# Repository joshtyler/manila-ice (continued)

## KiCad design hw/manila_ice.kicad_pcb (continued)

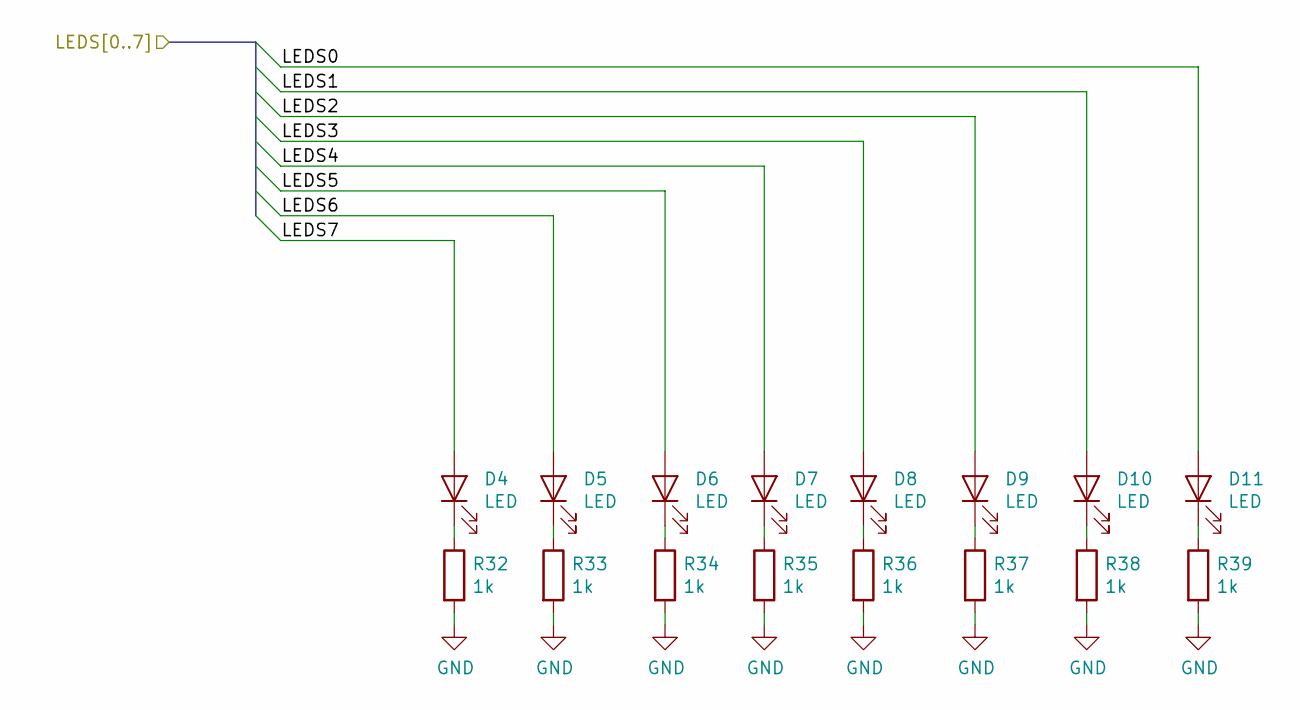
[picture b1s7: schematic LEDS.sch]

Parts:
D4, D5, D6, D7, D8, D9, D10, D11: LED; D_0805_2012Metric_Castellated; LCSC Part C84256
R32, R33, R34, R35, R36, R37, R38, R39: 1k; R_0603_1608Metric; LCSC Part C21190

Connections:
/FPGA/LED0: D11.2 (A); also elsewhere on the board
/FPGA/LED1: D10.2 (A); also elsewhere on the board
/FPGA/LED2: D9.2 (A); also elsewhere on the board
/FPGA/LED3: D8.2 (A); also elsewhere on the board
/FPGA/LED4: D7.2 (A); also elsewhere on the board
/FPGA/LED5: D6.2 (A); also elsewhere on the board
/FPGA/LED6: D5.2 (A); also elsewhere on the board
/FPGA/LED7: D4.2 (A); also elsewhere on the board
GND: R32.2, R33.2, R34.2, R35.2, R36.2, R37.2, R38.2, R39.2; also elsewhere on the board
unnamed: D4.1 (K), R32.1
unnamed: D5.1 (K), R33.1
unnamed: D6.1 (K), R34.1
unnamed: D7.1 (K), R35.1
unnamed: D8.1 (K), R36.1
unnamed: D9.1 (K), R37.1
unnamed: D10.1 (K), R38.1
unnamed: D11.1 (K), R39.1

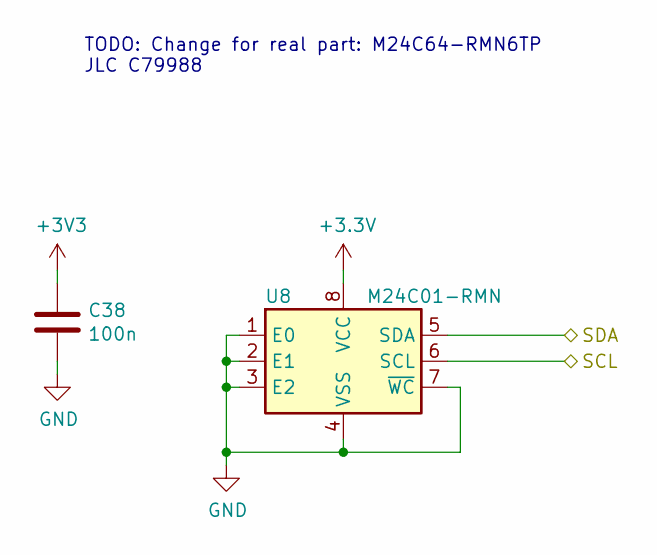
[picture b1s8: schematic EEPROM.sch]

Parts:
C38: 100n; C_0603_1608Metric; LCSC Part C14663
U8: M24C01-RMN; SOIC-8_3.9x4.9mm_P1.27mm; LCSC Part C79988

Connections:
/EEPROM/SCL: U8.6 (SCL); also elsewhere on the board
/EEPROM/SDA: U8.5 (SDA); also elsewhere on the board
GND: C38.2, U8.1 (E0), U8.2 (E1), U8.3 (E2), U8.4 (VSS), U8.7 (~WC); also elsewhere on the board

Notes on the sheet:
TODO: Change for real part: M24C64-RMN6TP JLC C79988

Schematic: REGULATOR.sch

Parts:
C10, C42, C43, C44: 22u; C_0603_1608Metric; LCSC Part C59461
C11, C41: 100n; C_0603_1608Metric; LCSC Part C14663
C12: 10p; C_0603_1608Metric; LCSC Part C1634
C39: 1n; C_0603_1608Metric; LCSC Part C1588
C40: 10n; C_0603_1608Metric; LCSC Part C57112
C45: 100u; CP_EIA-3528-21_Kemet-B; LCSC Part C16133
D12: SS54; D_SMA; LCSC Part C22452
L2: 2u2; L_Sunlord_MWSA0518; LCSC Part C408345
R43: 43k; R_0603_1608Metric; LCSC Part C23172
U3: TPS54331D; SOIC-8_3.9x4.9mm_P1.27mm; LCSC Part C9865

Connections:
+1V2: C42.1, C43.1, C44.1, C45.1, L2.2; also elsewhere on the board
/1V2_REG/BOOT: C41.1, U3.1 (BOOT)
/1V2_REG/COMP: C12.1, R43.1, U3.6 (COMP)
/1V2_REG/COMP_RC: C39.1, R43.2
/1V2_REG/FB: U3.5 (FB); also elsewhere on the board
/1V2_REG/PH: C41.2, D12.1 (K), L2.1, U3.8 (PH)
/1V2_REG/SS: C40.1, U3.4 (SS)
/5V: C10.1, C11.1, U3.2 (VIN); also elsewhere on the board
GND: C10.2, C11.2, C12.2, C39.2, C40.2, C42.2, C43.2, C44.2, C45.2, D12.2 (A), U3.7 (GND); also elsewhere on the board

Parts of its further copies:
C46, C52, C53, C54: 22u; C_0603_1608Metric; LCSC Part C59461
C47, C51: 100n; C_0603_1608Metric; LCSC Part C14663
C48: 10p; C_0603_1608Metric; LCSC Part C1634
C49: 1n; C_0603_1608Metric; LCSC Part C1588
C50: 10n; C_0603_1608Metric; LCSC Part C57112
C55: 100u; CP_EIA-3528-21_Kemet-B; LCSC Part C16133
D13: SS54; D_SMA; LCSC Part C22452
L3: 2u2; L_Sunlord_MWSA0518; LCSC Part C408345
R44: 43k; R_0603_1608Metric; LCSC Part C23172
U4: TPS54331D; SOIC-8_3.9x4.9mm_P1.27mm; LCSC Part C9865

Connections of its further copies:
/3V3_REG/BOOT: C51.1, U4.1 (BOOT)
/3V3_REG/COMP: C48.1, R44.1, U4.6 (COMP)
/3V3_REG/COMP_RC: C49.1, R44.2
/3V3_REG/FB: U4.5 (FB); also elsewhere on the board
/3V3_REG/PH: C51.2, D13.1 (K), L3.1, U4.8 (PH)
/3V3_REG/SS: C50.1, U4.4 (SS)
/5V: C46.1, C47.1, U4.2 (VIN); also elsewhere on the board
GND: C46.2, C47.2, C48.2, C49.2, C50.2, C52.2, C53.2, C54.2, C55.2, D13.2 (A), U4.7 (GND); also elsewhere on the board

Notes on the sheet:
3A max output. Designed using TI webench (tweaked from default values) Inductor value is a little low, but allows part reuse
Vref = 0.8V

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
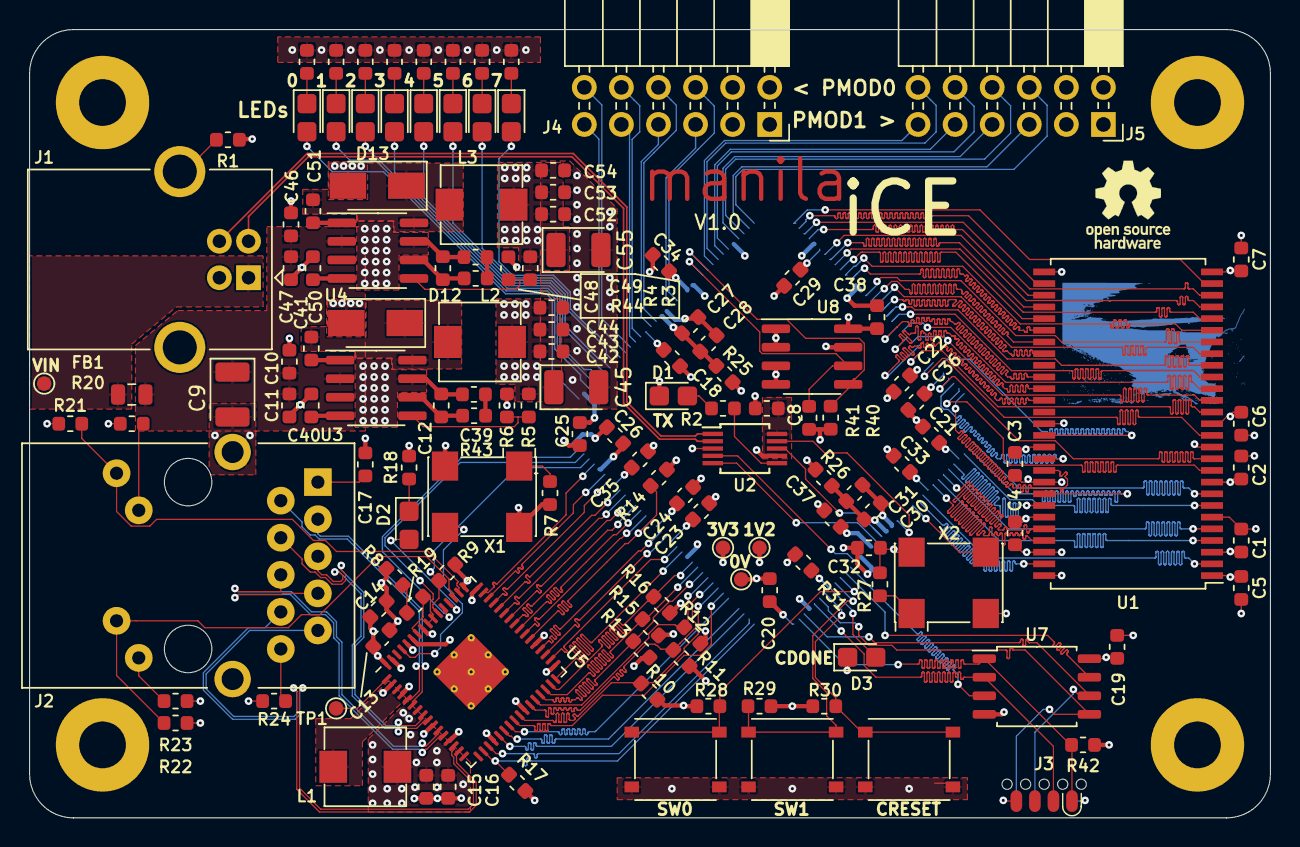
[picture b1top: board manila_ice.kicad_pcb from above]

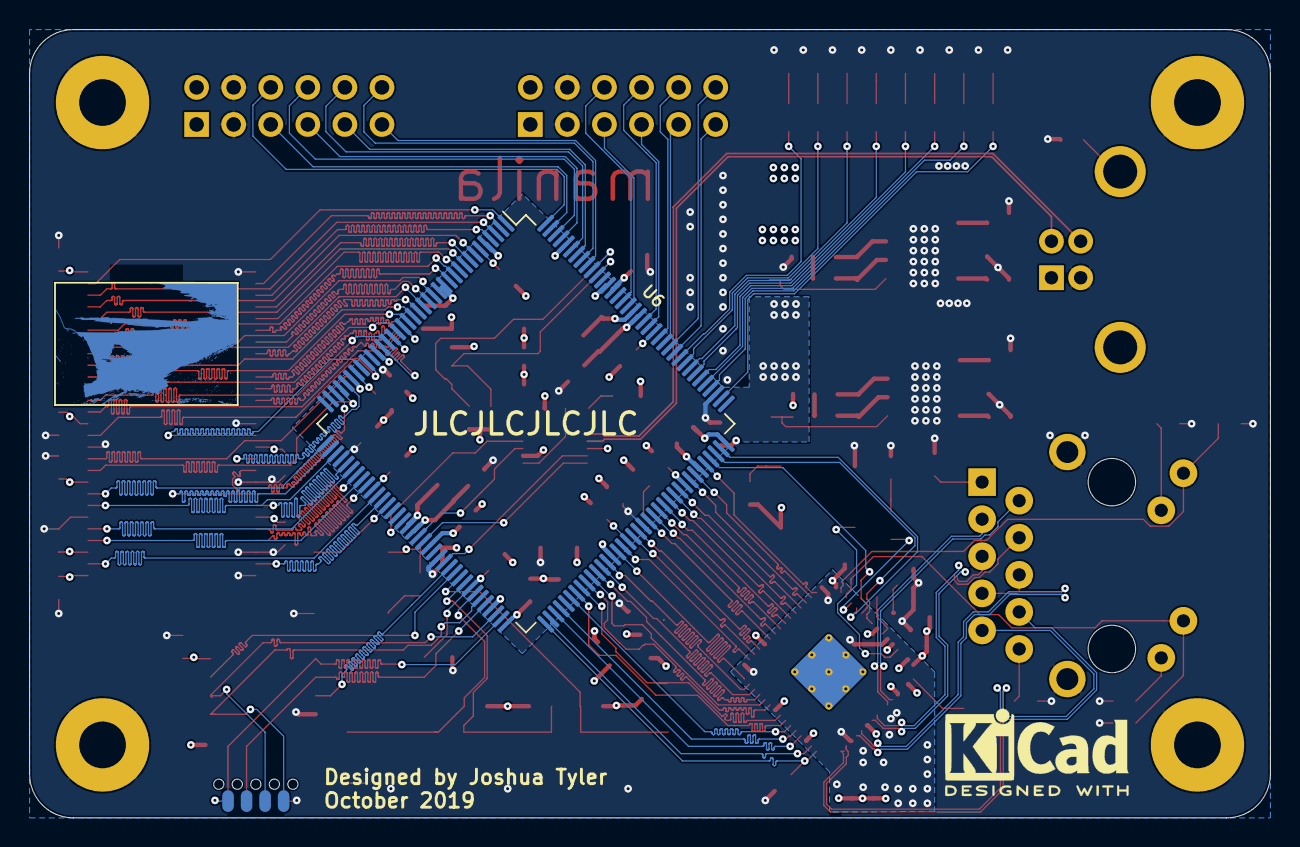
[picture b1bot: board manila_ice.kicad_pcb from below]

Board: 4 copper layers, 85.0 x 54.0 mm, 146 parts (3 on the bottom side), 166 nets.

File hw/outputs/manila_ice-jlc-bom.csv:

Comment,Designator,Footprint,LCSC Part #
100n Unpolarized capacitor,"C1,C2,C3,C4,C5,C6,C7,C8,C15,C13,C17,C27,C30,C21,C22,C24,C25,C20,C26,C19,C33,C32,C29,C23,C18,C34,C35,C36,C37,C38",C_0603_1608Metric,C14663
4u7 Unpolarized capacitor,"C11,C12,C10,C9,C16,C14,C28,C31",C_0603_1608Metric,C19666
LED Light emitting diode,"D1,D2,D3,D4,D5,D6,D7,D8,D9,D10,D11",D_0805_2012Metric_Castellated,C84256
GZ2012D101TF Ferrite bead,FB1,L_0805_2012Metric,C1015
4u7 Inductor,L1,R_0603_1608Metric,C19666
1k Resistor,"R1,R2,R31,R32,R33,R34,R35,R36,R37,R38,R39",R_0603_1608Metric,C21190
56k Resistor,R3,R_0603_1608Metric,C23206
18k Resistor,R5,R_0603_1608Metric,C25810
13k Resistor,R6,R_0603_1608Metric,C22797
91 Resistor,R8,R_0603_1608Metric,C25199
2k4 Resistor,R19,R_0603_1608Metric,C22940
510R Resistor,"R20,R23,R18",R_0603_1608Metric,C23193
4k7 Resistor,"R21,R22,R17,R15,R13,R12,R11,R16,R10,R14",R_0603_1608Metric,C23162
0R Resistor,R24,R_0603_1608Metric,C21189
100 Resistor,"R25,R26",R_0603_1608Metric,C22775
10k Resistor,"R41,R40,R4,R7,R9,R30,R29,R28,R27,R42",R_0603_1608Metric,C25804
SW_SPST Single Pole Single Throw (SPST) switch,"SW3,SW2,SW1",SW_Push_1P1T_NO_5.1x5.1mm,C318888
"W9812G6KH-6 128Mb Synchronous DRAM, 2 Mb x 16 b x 4 Banks, 166 MHz, TSOP-II-54",U1,TSOP-II-54_22.2x10.16mm_P0.8mm,C62379
"CH340E USB serial converter, UART, MSOP-10",U2,MSOP-10_3x3mm_P0.5mm,C99652
"TPS7A7001DDA 2A, Low-Dropout Voltage Regulator, 1.425-6.5V Input, Adjustable Min 0.5V Output, PowerPad SO-8","U4,U3",TI_SO-PowerPAD-8_ThermalVias,C60719
RTL8211EG-VB-CG 10/100/1000Mbps Ethernet Transceiver with RGMII/GMII/MII/RMII Interface,U5,QFN-64-1EP_9x9mm_P0.5mm_EP3.8x3.8mm_ThermalVias,C69264
"W25Q128JVS 128Mb Serial Flash Memory, Standard/Dual/Quad SPI, SOIC-8",U7,SOIC-8_5.23x5.23mm_P1.27mm,C97521
"M24C01-RMN 1Kb (128x8) I2C Serial EEPROM, 1.8-5.5V, SOIC-8",U8,SOIC-8_3.9x4.9mm_P1.27mm,C79988
SG-7050CAN CMOS Clock Oscillator,"X1,X2",Oscillator_SMD_SeikoEpson_SG8002CA-4Pin_7.0x5.0mm,C70528

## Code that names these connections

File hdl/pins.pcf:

# manila iCE constraints

set_io clk 49

set_io leds[0] 110
set_io leds[1] 112
set_io leds[2] 113
set_io leds[3] 114
set_io leds[4] 115
set_io leds[5] 116
set_io leds[6] 117
set_io leds[7] 118

set_io buttons[0] 63
set_io buttons[1] 64

set_io pmod0[0] 119
set_io pmod0[1] 120
set_io pmod0[2] 121
set_io pmod0[3] 122
set_io pmod0[4] 124
set_io pmod0[5] 125
set_io pmod0[6] 128
set_io pmod0[7] 129

set_io pmod1[0] 136
set_io pmod1[1] 137
set_io pmod1[2] 138
set_io pmod1[3] 139
set_io pmod1[4] 141
set_io pmod1[5] 142
set_io pmod1[6] 143
set_io pmod1[7] 144

set_io uart_tx    52
set_io uart_rx    55
set_io uart_cts_n 56
set_io uart_rts_n 60

set_io spi_mosi   67
set_io spi_miso   68
set_io spi_sck    70
set_io spi_ss     71
set_io spi_wp_n   61
set_io spi_hold_n 62

set_io i2c_scl  130
set_io i2c_wc_n 134
set_io i2c_sda  135

set_io eth_phyrst_n  93
set_io eth_rxdv      73
set_io eth_gtxclk    88
set_io eth_txen      90
set_io eth_txer      104
set_io eth_rxclk     79
set_io eth_rxer      84
set_io eth_col       85
set_io eth_cs        87
set_io eth_txclk     97
set_io eth_mdio      105
set_io eth_mdc       107
set_io eth_pme_int_n 106
set_io eth_rxd[0]    74
set_io eth_rxd[1]    75
set_io eth_rxd[2]    76
set_io eth_rxd[3]    78
set_io eth_rxd[4]    80
set_io eth_rxd[5]    81
set_io eth_rxd[6]    82
set_io eth_rxd[7]    83
set_io eth_txd[0]    91
set_io eth_txd[1]    94
set_io eth_txd[2]    95
set_io eth_txd[3]    96
set_io eth_txd[4]    98
set_io eth_txd[5]    99
set_io eth_txd[6]    101
set_io eth_txd[7]    102

set_io sdram_clk      23
set_io sdram_cke      21
set_io sdram_cs_n     19
set_io sdram_ras_n    20
set_io sdram_cas_n    22
set_io sdram_we_n     24
set_io sdram_bs[0]    17
set_io sdram_bs[1]    15
set_io sdram_addr[0]  9
set_io sdram_addr[1]  7
set_io sdram_addr[2]  3
set_io sdram_addr[3]  1
set_io sdram_addr[4]  2
set_io sdram_addr[5]  4
set_io sdram_addr[6]  8
set_io sdram_addr[7]  10
set_io sdram_addr[8]  12
set_io sdram_addr[9]  16
set_io sdram_addr[10] 11
set_io sdram_addr[11] 18
set_io sdram_data[0]  47
set_io sdram_data[1]  44
set_io sdram_data[2]  42
set_io sdram_data[3]  39
set_io sdram_data[4]  37
set_io sdram_data[5]  33
set_io sdram_data[6]  31
set_io sdram_data[7]  28
set_io sdram_data[8]  29
set_io sdram_data[9]  32
set_io sdram_data[10] 34
set_io sdram_data[11] 38
set_io sdram_data[12] 41
set_io sdram_data[13] 43
set_io sdram_data[14] 45
set_io sdram_data[15] 48
set_io sdram_dqm[0]   26
set_io sdram_dqm[1]   25

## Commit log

2019-09-29 First complete commit
2019-10-07 Commit before messing with via sizes for JLC compliance
2019-10-07 Pre tuning of DDR length matching
2019-10-08 Fully routed
2019-10-13 PMODs corrected
2019-10-15 Basically done.
2019-10-17 Add EEPROM
2019-10-19 Tidy up
2019-10-19 Change folder structure
2019-10-19 Add kicad-footprints and kicad-symbols used for this project as submodules.
    This is done because not all prs have been merged into kicad master yet.
2019-10-19 Add outputs folder
2019-10-19 Rename project
2019-10-19 Add forgotten pullup to SPI flash ~CS
2019-10-19 Add comment
2019-10-19 Add fab outputs
2019-10-19 Finished except some parts need to be rotated
2019-10-21 Add ability to rotate part for JLC PCB
2019-10-21 Replace ethernet SMPS inductor with a sensible power rating
2019-10-22 Added ground pour on bottom. Fixed DRC errors
2019-10-23 Move to switched mode regulators. Layout not complete yet
2019-10-23 Plumbed in SMPS
2019-10-24 Resize refdes
2019-10-24 Change submodule to point at my fork since I've made a commit
2019-10-24 Minor tweak to font size
2019-10-27 Fixed tant footprint. Added JLC part numbers to other components
2019-10-27 Add ESD protection
2019-10-27 Make refdes size uniform
2019-10-28 Fix JLC rotation
2019-10-31 Changed stackup to JLC7628
2019-11-02 Remove all thin traces from power nets
2019-11-02 Update schematic to change slew rates of PSUs and to add switch debouncing
2019-11-02 Schematic tweaks
2019-11-03 Ready for fab
2019-11-10 Add HDL folder
2019-11-11 Add working UART
2019-11-11 Re-add hdl_commmon folder. I messed it up somehow
2019-11-11 Fix makefile now files have moved to common structure
2019-12-19 Additions
2020-01-02 Remove accidentally committed file
2020-01-04 Basic UART working
2020-02-02 Fixup makefiles. Stop recording VCD for speed
2020-02-02 Inital bootstrap stuff. Simple wb example working
2020-02-02 Move submodule
2020-02-02 Working with moved hdl_common
2020-02-13 Steps towards bootstrap support in hx4k dev board
2020-02-25 Basic sim working
2020-02-25 Reading device ID in sim
2020-03-03 Able to program flash fairly quickly. Not working at 2M baud for an unknown reason
2020-03-04 Multiboot to second partition working
2020-03-05 Add experimental flow control support
2020-03-08 Add spi data injection/extraction. Not currently working in hardware
2020-03-08 Correct pinout for UART flow control
2020-03-08 Add spi_prog as a submodule, so we can track development with the hdl
2020-03-16 Update spi_prog
2020-03-16 Update spi_prog to include gitignore
2020-03-16 Add .gitignore to bootstrap project
2020-03-16 Add sdram_test
2020-04-11 Playing back SPI commands at boot working
2020-04-11 Working correctly with volatile protection on boot
2020-04-18 SDRAM controller working in hardware
2020-04-18 Working in hardware
2020-04-18 Working with incrementing address
2020-04-19 sdram test working full width and full address space
2020-04-19 Add more tests
2020-04-20 Add ethernet loopback test
2020-04-26 Bootstrap working with buttons to select image
2020-04-26 Add program to peek and poke registers
2020-04-26 Add script to find the serial device a manila ice is connected to
2020-04-26 Stop serial_wb_master from bursting passed the end of a component
2020-04-28 Support sending out version string on boot
2020-05-03 Modify bootloader to unlock after magic is received
2020-05-03 Initial commit of scripts to program manila iCE
2020-05-08 [REFACTOR] correct spelling
2020-05-08 Add flash layout diagram
2020-05-08 Installing scripts working
2020-05-08 Split out multiboot into separate makefile
2020-05-08 Minor corrections
2020-05-08 Reading serial number when programming
2020-05-08 Remove hardcoded serial port
2020-05-08 Add readme
2020-05-09 Remove out of date software application
2020-05-09 Stop sending dummy byte now that we have the unlock procedure
2020-05-09 Move to template Makefile
2020-05-09 Move example project to use makefile template
2020-05-09 Increase timeout and recognise when the board has output nothing
2020-05-09 Move to common pcf file for all builds
2020-05-09 Remove fp-info-cache
2020-05-09 Remove kicad footprints and kicad symbols submodules
    These symbols are all cached in the schematic, and will be upstream eventually anyway
2020-05-09 Update readme following tag
2020-05-26 Allow programming from literal address
2020-05-26 Basic picorv32 working (although only in default SPI mode at the moment)
2020-05-31 Update submodules
2020-06-06 Basic picosoc working on manila ice
2020-06-06 Simplified example
2020-07-28 UIP binary compiling
2020-10-12 GE and SoC in design together. WIP
2020-12-29 Update for new common code
2020-12-29 Update submodules]
2020-12-29 Begin project for FGPA TCP interface
2021-01-09 Draft of ARP handler
2021-02-27 Working in simuation, but not in reality (payload has correct CRC, but is all zeros
2021-02-28 Exposed hardware bug in post-synth simulation
2021-02-28 Update scipts so that manila installs with CMake build. Needs to be improved, it's hacky becuase I wanted to get it working...
2021-02-28 Exposed bug in sim by breaking out debug signals
2021-02-28 Added workaround for yosys bug. ARP working in hardware - even though it is not quite meeting timing!
2021-03-02 ARP Working and meeting timing
